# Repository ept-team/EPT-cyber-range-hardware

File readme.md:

preliminary release of hardware for the ept cyber range

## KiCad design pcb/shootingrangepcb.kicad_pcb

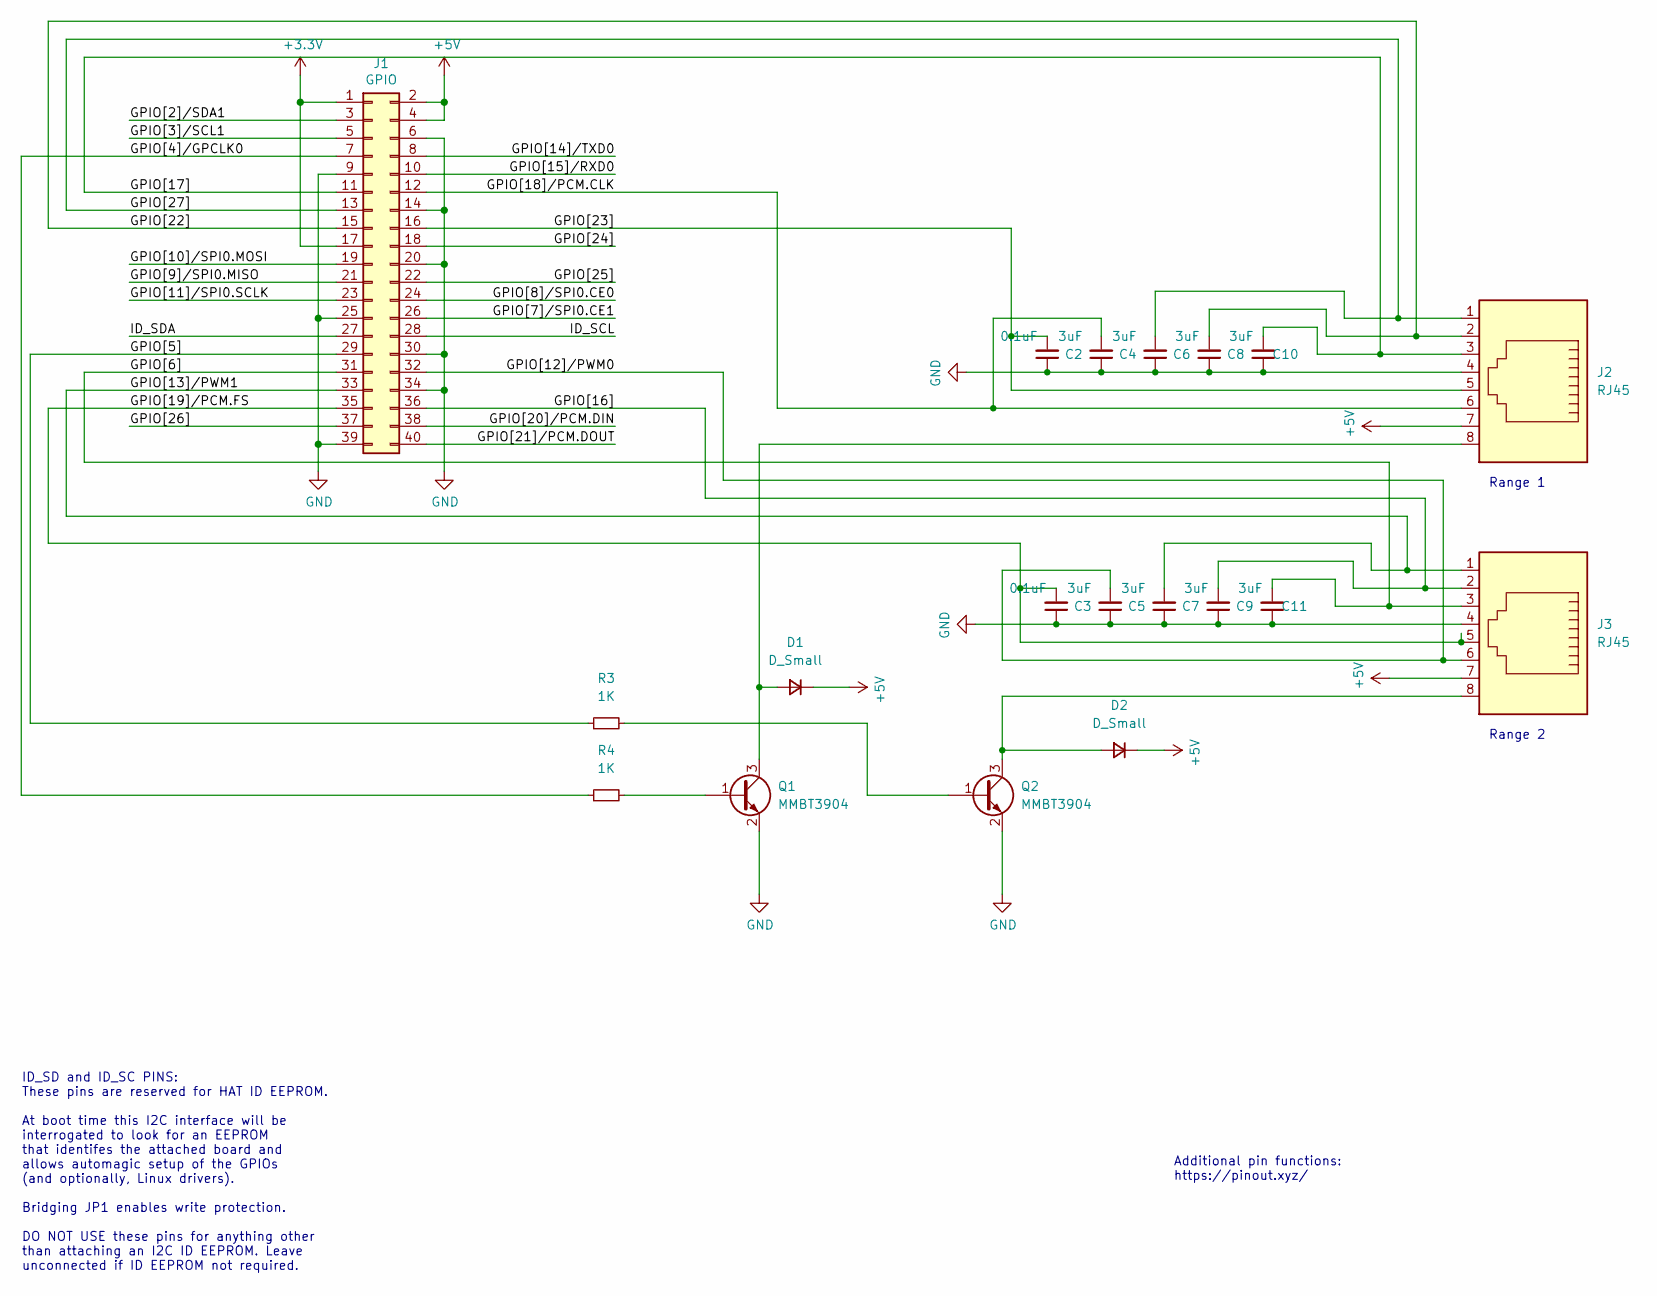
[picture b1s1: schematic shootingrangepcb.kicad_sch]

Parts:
C2, C3: 0.1uF; C_1206_3216Metric_Pad1.33x1.80mm_HandSolder
C4, C5, C6, C7, C8, C9, C10, C11: 3uF; C_1206_3216Metric_Pad1.33x1.80mm_HandSolder
D1, D2: D_Small; D_SMA_Handsoldering
J1: GPIO; PinSocket_2x20_P2.54mm_Vertical
J2, J3: RJ45; TE_1-215877-3
Q1, Q2: MMBT3904; SOT-23
R3, R4: 1K; R_1206_3216Metric_Pad1.30x1.75mm_HandSolder

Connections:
+3V3: J1.1, J1.17
+5V: D1.1 (K), D2.1 (K), J1.2, J1.4, J2.7, J3.7
/GPIO[2]/SDA1: J1.3
/GPIO[3]/SCL1: J1.5
/GPIO[4]/GPCLK0: J1.7, R4.1
/GPIO[5]: J1.29, R3.1
/GPIO[6]: C11.2, J1.31, J3.3
/GPIO[7]/SPI0.CE1: J1.26
/GPIO[8]/SPI0.CE0: J1.24
/GPIO[9]/SPI0.MISO: J1.21
/GPIO[10]/SPI0.MOSI: J1.19
/GPIO[11]/SPI0.SCLK: J1.23
/GPIO[12]/PWM0: C5.2, J1.32, J3.6
/GPIO[13]/PWM1: C7.2, J1.33, J3.1
/GPIO[14]/TXD0: J1.8
/GPIO[15]/RXD0: J1.10
/GPIO[16]: C9.2, J1.36, J3.2
/GPIO[17]: C10.2, J1.11, J2.3
/GPIO[18]/PCM.CLK: C4.2, J1.12, J2.6
/GPIO[19]/PCM.FS: C3.2, J1.35, J3.5
/GPIO[20]/PCM.DIN: J1.38
/GPIO[21]/PCM.DOUT: J1.40
/GPIO[22]: C8.2, J1.15, J2.2
/GPIO[23]: C2.2, J1.16, J2.5
/GPIO[24]: J1.18
/GPIO[25]: J1.22
/GPIO[26]: J1.37
/GPIO[27]: C6.2, J1.13, J2.1
/ID_SCL: J1.28
/ID_SDA: J1.27
GND: C2.1, C3.1, C4.1, C5.1, C6.1, C7.1, C8.1, C9.1, C10.1, C11.1, J1.6, J1.9, J1.14, J1.20, J1.25, J1.30, J1.34, J1.39, J2.4, J3.4, Q1.2 (E), Q2.2 (E)
unnamed: D1.2 (A), J2.8, Q1.3 (C)
unnamed: D2.2 (A), J3.8, Q2.3 (C)
unnamed: Q1.1 (B), R4.2
unnamed: Q2.1 (B), R3.2

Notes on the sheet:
Range 1
Additional pin functions: https://pinout.xyz/
Range 2
ID_SD and ID_SC PINS: These pins are reserved for HAT ID EEPROM. At boot time this I2C interface will be interrogated to look for an EEPROM that identifes the attached board and allows automagic setup of the GPIOs (and optionally, Linux drivers). Bridging JP1 enables write protection. DO NOT USE th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

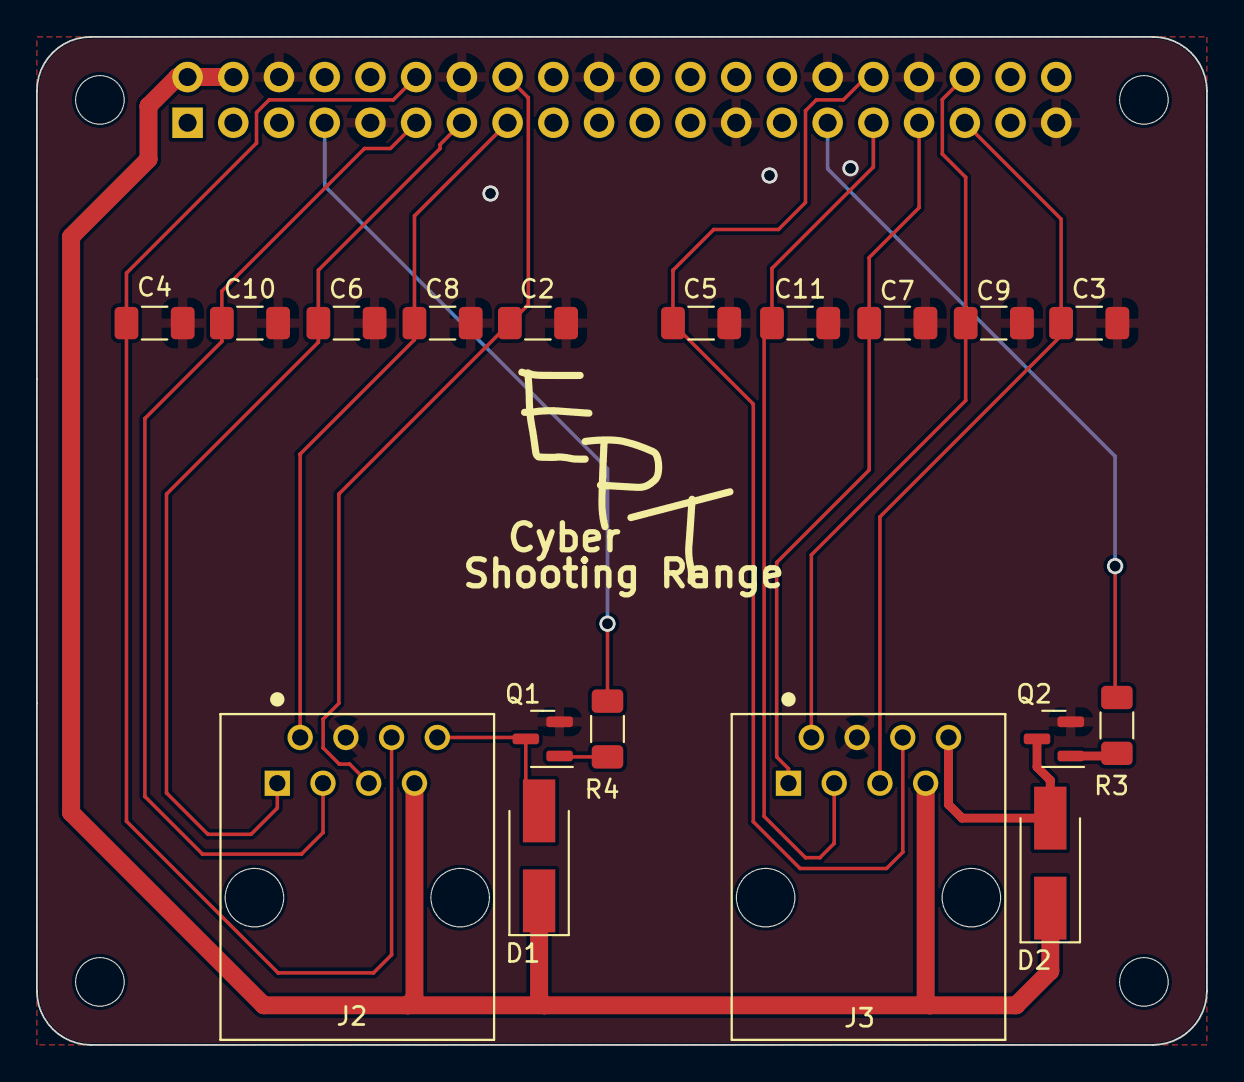
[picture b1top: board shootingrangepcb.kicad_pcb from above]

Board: 2 copper layers, 65.0 x 56.0 mm, 24 parts (1 on the bottom side), 19 nets.

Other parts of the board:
 : LOGO; ept_kicad_file
MH1, MH2, MH3, MH4: MountingHole_2.7mm_M2.5

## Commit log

2025-11-11 added readme
